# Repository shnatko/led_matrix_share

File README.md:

# led_matrix_share
Eagle files for LED matrix control board / analog mux array for IR sensing

Details on the build of the LED matrix ( in coffee table form ) can be found at http://shnatko.tumblr.com

The control_FET files contain the schematic and board files for a single 8x8 common anode 8x8 RGB LED array driving via SPI 
from a microcontroller ( Arduino Due in my case ).
Multiple boards can be chained together to form larger arrays ( matrix I built using them is 16x32 )

The sense_mux files are for a second PCB used to multiplex 64 analog input signals down to 4 outputs pins for input into
the microcontroller.  Again, additional details on how it is used at http://shnatko.tumblr.com

Also included in this package is the MBI.lbr Eagle library in which I created a few components which I needed for the board layout.

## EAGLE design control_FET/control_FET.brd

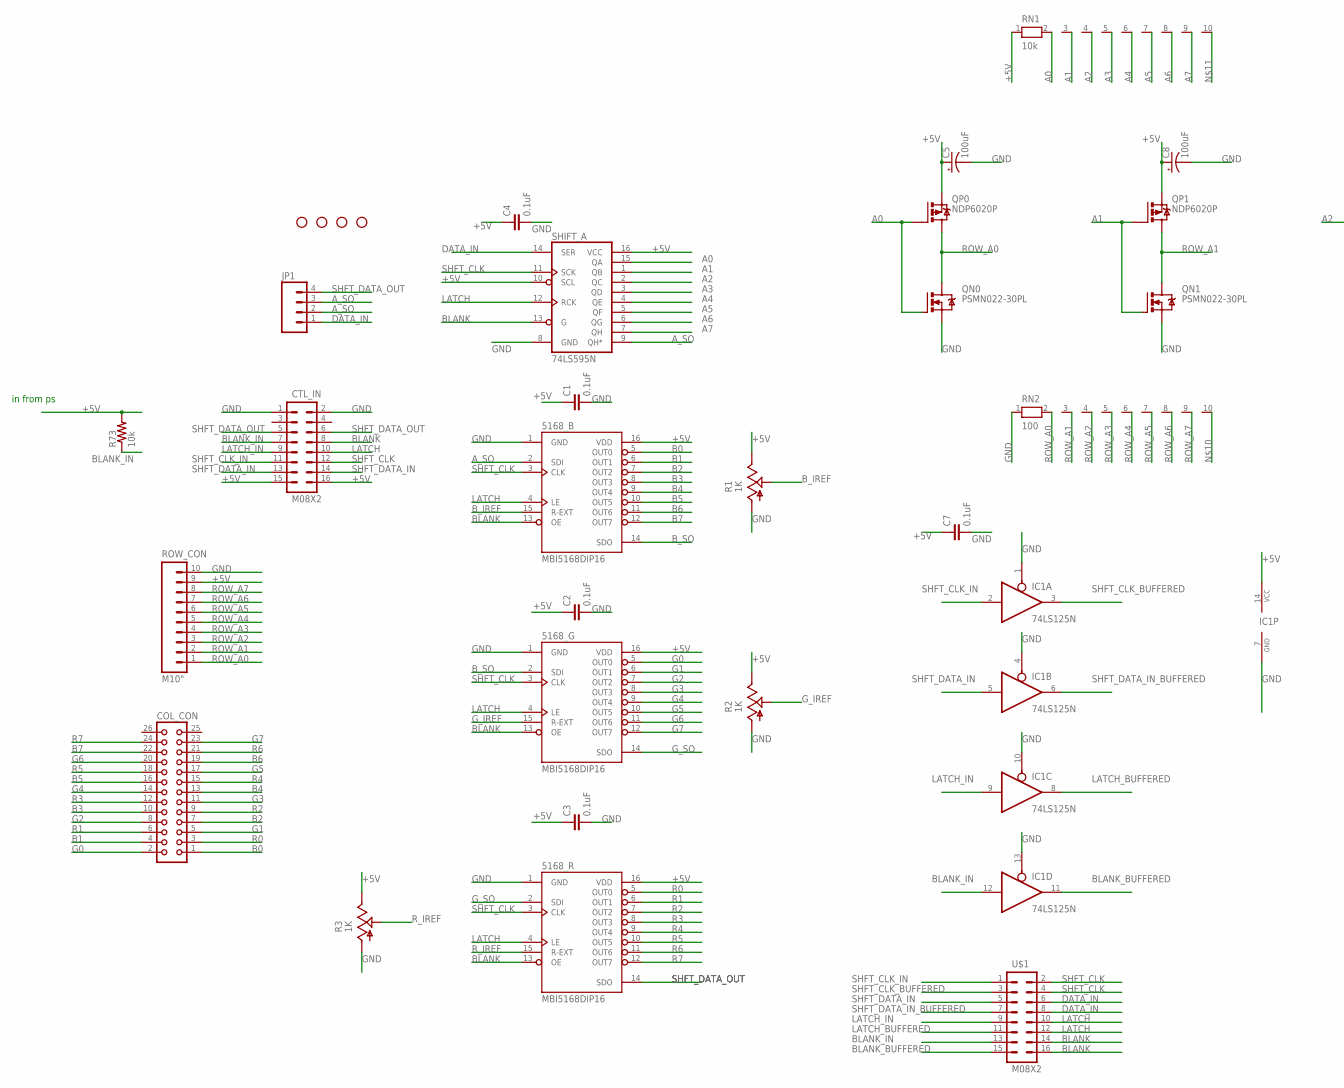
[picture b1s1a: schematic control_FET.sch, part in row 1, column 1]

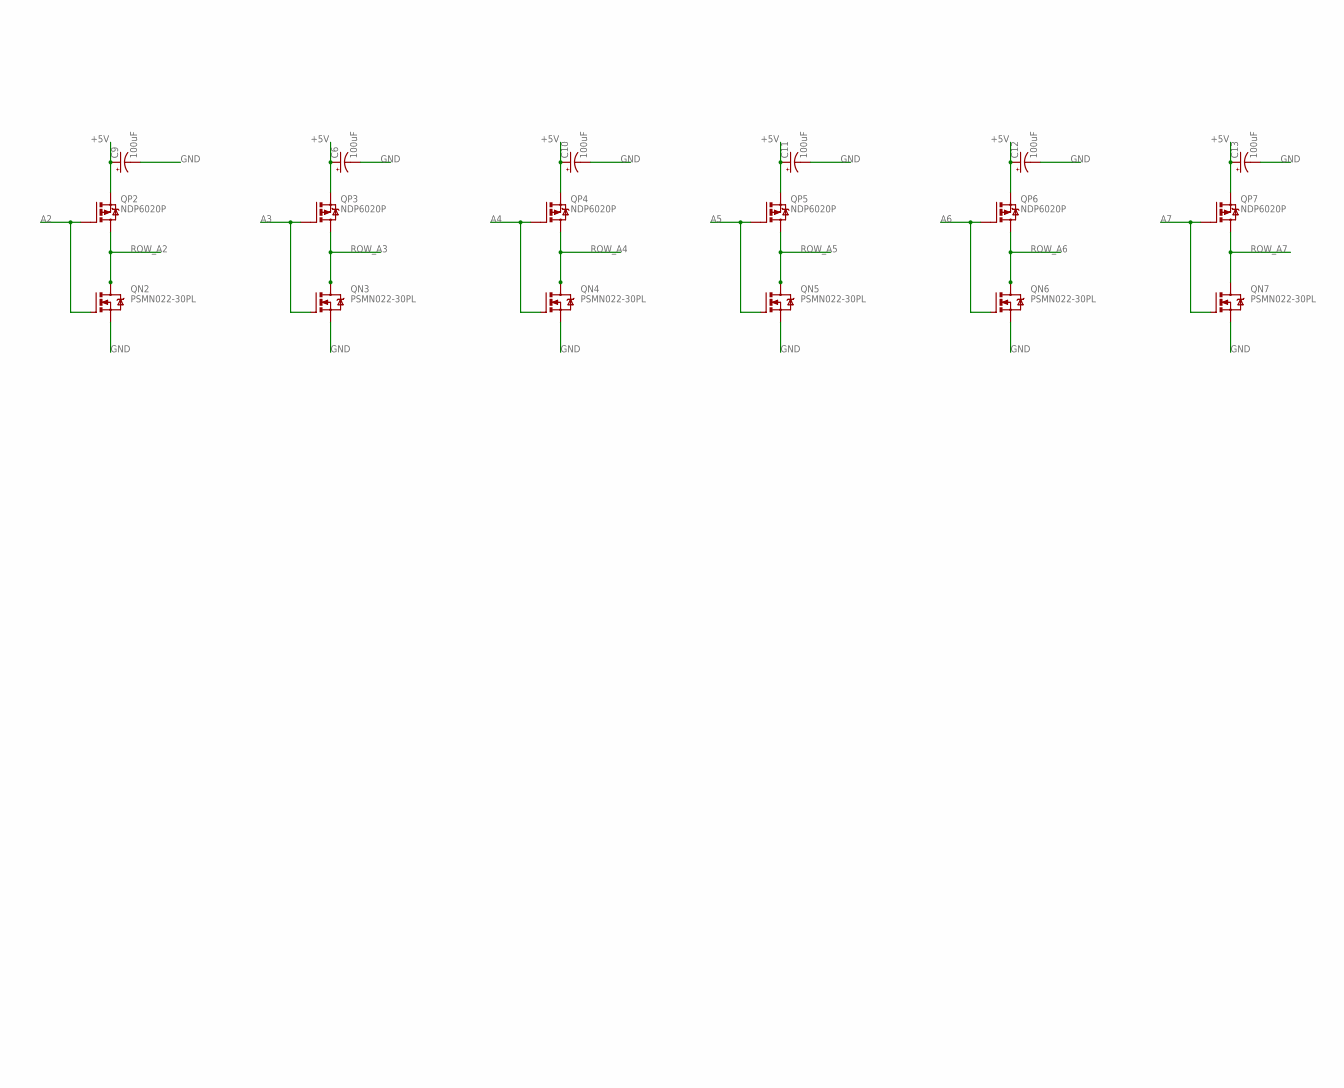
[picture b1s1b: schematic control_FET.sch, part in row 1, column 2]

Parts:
5168_B, 5168_G, 5168_R: MBI5168DIP16; DIL16
C1, C2, C3, C4, C7: 0.1uF; C2.5-3
C5, C6, C8, C9, C10, C11, C12, C13: 100uF; CPOL-RADIAL-100UF-25V
COL_CON: CON26
CTL_IN: M08X2; 2X8
IC1: 74LS125N; DIL14
JP1: M04PTH; 1X04
QN0, QN1, QN2, QN3, QN4, QN5, QN6, QN7: PSMN022-30PL; TO220BV
QP0, QP1, QP2, QP3, QP4, QP5, QP6, QP7: NDP6020P; TO220BV
R1, R2, R3: 1K; CA6V
R73: 10k; 0207/10
RN1: 10k; RN-10
RN2: 100; RN-10
ROW_CON: M10"; 1X10
SHIFT_A: 74LS595N; DIL16
STANDOFF1, STANDOFF2, STANDOFF3, STANDOFF4: STAND-OFF
U$1: M08X2; 2X8

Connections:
+5V: 5168_B.16 (VDD), 5168_G.16 (VDD), 5168_R.16 (VDD), C1.1, C2.1, C3.1, C4.1, C5.1 (+), C6.1 (+), C7.1, C8.1 (+), C9.1 (+), C10.1 (+), C11.1 (+), C12.1 (+), C13.1 (+), CTL_IN.15, CTL_IN.16, IC1.14 (VCC), QP0.S, QP1.S, QP2.S, QP3.S, QP4.S, QP5.S, QP6.S, QP7.S, R1.E, R2.E, R3.E, R73.2, RN1.1, ROW_CON.9, SHIFT_A.10 (SCL), SHIFT_A.16 (VCC)
A0: QN0.G, QP0.G, RN1.2, SHIFT_A.15 (QA)
A1: QN1.G, QP1.G, RN1.3, SHIFT_A.1 (QB)
A2: QN2.G, QP2.G, RN1.4, SHIFT_A.2 (QC)
A3: QN3.G, QP3.G, RN1.5, SHIFT_A.3 (QD)
A4: QN4.G, QP4.G, RN1.6, SHIFT_A.4 (QE)
A5: QN5.G, QP5.G, RN1.7, SHIFT_A.5 (QF)
A6: QN6.G, QP6.G, RN1.8, SHIFT_A.6 (QG)
A7: QN7.G, QP7.G, RN1.9, SHIFT_A.7 (QH)
A_SO: 5168_B.2 (SDI), JP1.2, JP1.3, SHIFT_A.9 (QH*)
B0: 5168_B.5 (OUT0), COL_CON.1
B1: 5168_B.6 (OUT1), COL_CON.4
B2: 5168_B.7 (OUT2), COL_CON.7
B3: 5168_B.8 (OUT3), COL_CON.10
B4: 5168_B.9 (OUT4), COL_CON.13
B5: 5168_B.10 (OUT5), COL_CON.16
B6: 5168_B.11 (OUT6), COL_CON.19
B7: 5168_B.12 (OUT7), COL_CON.22
BLANK: 5168_B.13 (OE), 5168_G.13 (OE), 5168_R.13 (OE), CTL_IN.8, SHIFT_A.13 (G), U$1.14, U$1.16
BLANK_BUFFERED: IC1.11 (O), U$1.15
BLANK_IN: CTL_IN.7, IC1.12 (I), R73.1, U$1.13
B_IREF: 5168_B.15 (R-EXT), R1.S
B_SO: 5168_B.14 (SDO), 5168_G.2 (SDI)
DATA_IN: JP1.1, SHIFT_A.14 (SER), U$1.6, U$1.8
G0: 5168_G.5 (OUT0), COL_CON.2
G1: 5168_G.6 (OUT1), COL_CON.5
G2: 5168_G.7 (OUT2), COL_CON.8
G3: 5168_G.8 (OUT3), COL_CON.11
G4: 5168_G.9 (OUT4), COL_CON.14
G5: 5168_G.10 (OUT5), COL_CON.17
G6: 5168_G.11 (OUT6), COL_CON.20
G7: 5168_G.12 (OUT7), COL_CON.23
GND: 5168_B.1 (GND), 5168_G.1 (GND), 5168_R.1 (GND), C1.2, C2.2, C3.2, C4.2, C5.2 (-), C6.2 (-), C7.2, C8.2 (-), C9.2 (-), C10.2 (-), C11.2 (-), C12.2 (-), C13.2 (-), CTL_IN.1, CTL_IN.2, IC1.1 (OE), IC1.4 (OE), IC1.7 (GND), IC1.10 (OE), IC1.13 (OE), QN0.S, QN1.S, QN2.S, QN3.S, QN4.S, QN5.S, QN6.S, QN7.S, R1.A, R2.A, R3.A, RN2.1, ROW_CON.10, SHIFT_A.8 (GND)
G_IREF: 5168_G.15 (R-EXT), R2.S
G_SO: 5168_G.14 (SDO), 5168_R.2 (SDI)
LATCH: 5168_B.4 (LE), 5168_G.4 (LE), 5168_R.4 (LE), CTL_IN.10, SHIFT_A.12 (RCK), U$1.10, U$1.12
LATCH_BUFFERED: IC1.8 (O), U$1.11
LATCH_IN: CTL_IN.9, IC1.9 (I), U$1.9
R0: 5168_R.5 (OUT0), COL_CON.3
R1: 5168_R.6 (OUT1), COL_CON.6
R2: 5168_R.7 (OUT2), COL_CON.9
R3: 5168_R.8 (OUT3), COL_CON.12
R4: 5168_R.9 (OUT4), COL_CON.15
R5: 5168_R.10 (OUT5), COL_CON.18
R6: 5168_R.11 (OUT6), COL_CON.21
R7: 5168_R.12 (OUT7), COL_CON.24
ROW_A0: QN0.D, QP0.D, RN2.2, ROW_CON.1
ROW_A1: QN1.D, QP1.D, RN2.3, ROW_CON.2
ROW_A2: QN2.D, QP2.D, RN2.4, ROW_CON.3
ROW_A3: QN3.D, QP3.D, RN2.5, ROW_CON.4
ROW_A4: QN4.D, QP4.D, RN2.6, ROW_CON.5
ROW_A5: QN5.D, QP5.D, RN2.7, ROW_CON.6
ROW_A6: QN6.D, QP6.D, RN2.8, ROW_CON.7
ROW_A7: QN7.D, QP7.D, RN2.9, ROW_CON.8
R_IREF: 5168_R.15 (R-EXT), R3.S
SHFT_CLK: 5168_B.3 (CLK), 5168_G.3 (CLK), 5168_R.3 (CLK), CTL_IN.12, SHIFT_A.11 (SCK), U$1.2, U$1.4
SHFT_CLK_BUFFERED: IC1.3 (O), U$1.3
SHFT_CLK_IN: CTL_IN.11, IC1.2 (I), U$1.1
SHFT_DATA_IN: CTL_IN.13, CTL_IN.14, IC1.5 (I), U$1.5
SHFT_DATA_IN_BUFFERED: IC1.6 (O), U$1.7
SHFT_DATA_OUT: 5168_R.14 (SDO), CTL_IN.5, CTL_IN.6, JP1.4

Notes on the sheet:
in from ps

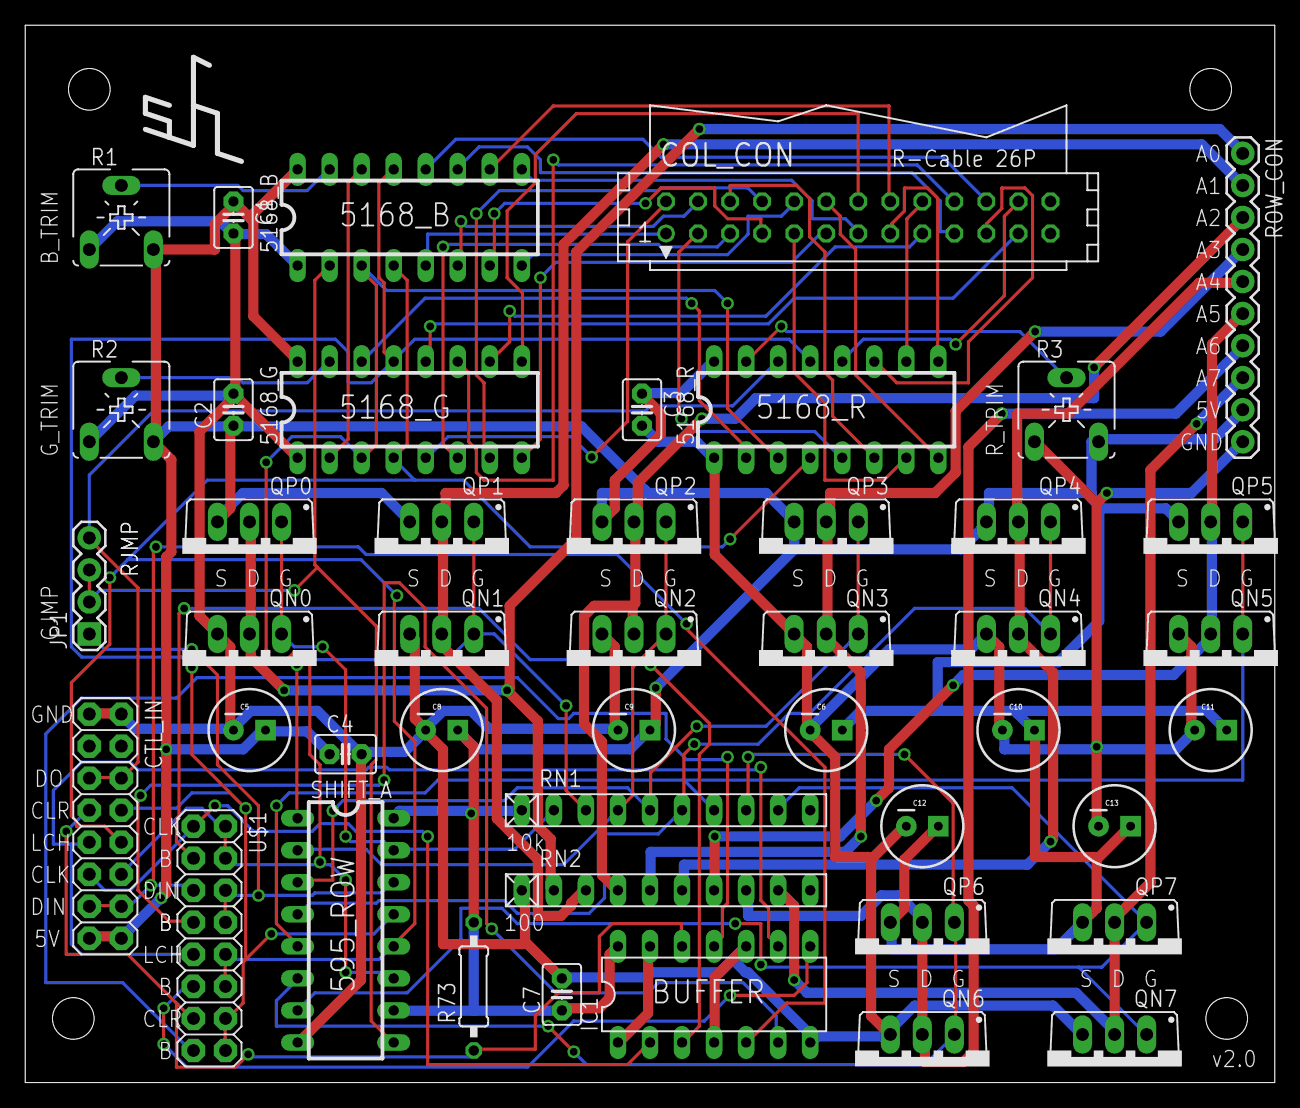
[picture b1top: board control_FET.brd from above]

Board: 2 copper layers, 99.1 x 83.8 mm, 49 parts (0 on the bottom side), 61 nets.

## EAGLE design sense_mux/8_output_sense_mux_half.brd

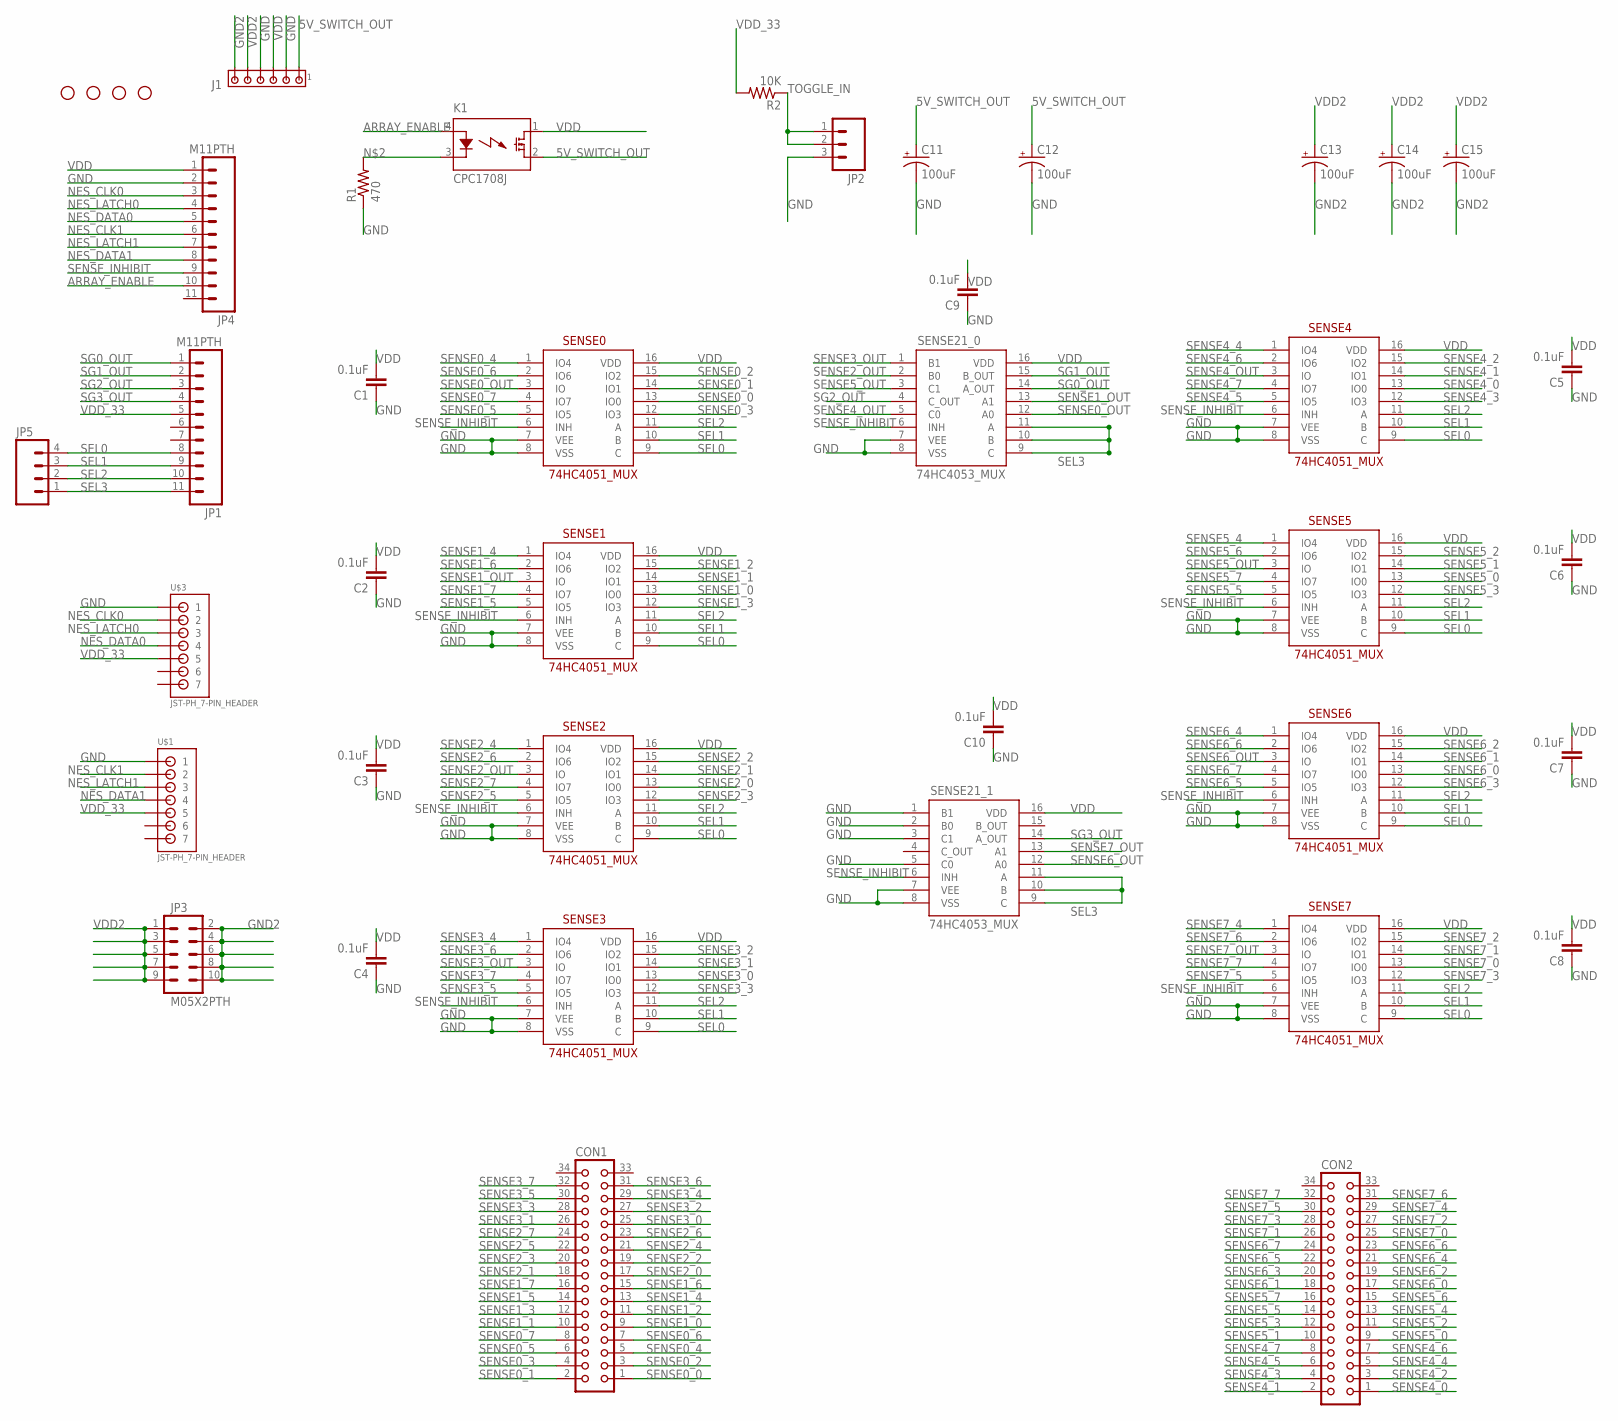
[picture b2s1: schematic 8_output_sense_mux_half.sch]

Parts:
C1, C2, C3, C4, C5, C6, C7, C8, C9, C10: 0.1uF; C2.5-3
C11, C12, C13, C14, C15: 100uF; CPOL-RADIAL-100UF-25V
CON1, CON2: CON34
J1: MTA06-156; 1X6MTA
JP1, JP4: M11PTH; 1X11
JP2: M03PTH; 1X03
JP3: M05X2PTH; AVR_ICSP
JP5: M04PTH; 1X04
K1: CPC1708J; I4-PAC
R1: 470; AXIAL-0.3-KIT
R2: 10K; AXIAL-0.3-KIT
SENSE0, SENSE1, SENSE2, SENSE3, SENSE4, SENSE5, SENSE6, SENSE7: 74HC4051_MUX; DIL16
SENSE21_0, SENSE21_1: 74HC4053_MUX; DIL16
STANDOFF1, STANDOFF2, STANDOFF3, STANDOFF4: STAND-OFF
U$1, U$3: JST-PH_7-PIN_HEADER; JST_B7B-PH_HEADER

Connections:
5V_SWITCH_OUT: C11.1 (+), C12.1 (+), J1.1, K1.2 (DS2)
ARRAY_ENABLE: JP4.10, K1.4 (A)
GND: C1.1, C2.1, C3.1, C4.1, C5.1, C6.1, C7.1, C8.1, C9.1, C10.1, C11.2 (-), C12.2 (-), J1.2, J1.4, JP2.3, JP4.2, R1.P$1 (1), SENSE0.7 (VEE), SENSE0.8 (VSS), SENSE1.7 (VEE), SENSE1.8 (VSS), SENSE2.7 (VEE), SENSE2.8 (VSS), SENSE3.7 (VEE), SENSE3.8 (VSS), SENSE4.7 (VEE), SENSE4.8 (VSS), SENSE5.7 (VEE), SENSE5.8 (VSS), SENSE6.7 (VEE), SENSE6.8 (VSS), SENSE7.7 (VEE), SENSE7.8 (VSS), SENSE21_0.7 (VEE), SENSE21_0.8 (VSS), SENSE21_1.1 (B1), SENSE21_1.2 (B0), SENSE21_1.3 (C1), SENSE21_1.5 (C0), SENSE21_1.7 (VEE), SENSE21_1.8 (VSS), U$1.P1 (1), U$3.P1 (1)
GND2: C13.2 (-), C14.2 (-), C15.2 (-), J1.6, JP3.2, JP3.4, JP3.6, JP3.8, JP3.10
unnamed: K1.3 (K), R1.P$2 (2)
NES_CLK0: JP4.3, U$3.P2 (2)
NES_CLK1: JP4.6, U$1.P2 (2)
NES_DATA0: JP4.5, U$3.P4 (4)
NES_DATA1: JP4.8, U$1.P4 (4)
NES_LATCH0: JP4.4, U$3.P3 (3)
NES_LATCH1: JP4.7, U$1.P3 (3)
SEL0: JP1.8, JP5.4, SENSE0.9 (C), SENSE1.9 (C), SENSE2.9 (C), SENSE3.9 (C), SENSE4.9 (C), SENSE5.9 (C), SENSE6.9 (C), SENSE7.9 (C)
SEL1: JP1.9, JP5.3, SENSE0.10 (B), SENSE1.10 (B), SENSE2.10 (B), SENSE3.10 (B), SENSE4.10 (B), SENSE5.10 (B), SENSE6.10 (B), SENSE7.10 (B)
SEL2: JP1.10, JP5.2, SENSE0.11 (A), SENSE1.11 (A), SENSE2.11 (A), SENSE3.11 (A), SENSE4.11 (A), SENSE5.11 (A), SENSE6.11 (A), SENSE7.11 (A)
SEL3: JP1.11, JP5.1, SENSE21_0.9 (C), SENSE21_0.10 (B), SENSE21_0.11 (A), SENSE21_1.9 (C), SENSE21_1.10 (B), SENSE21_1.11 (A)
SENSE0_0: CON1.1, SENSE0.13 (IO0)
SENSE0_1: CON1.2, SENSE0.14 (IO1)
SENSE0_2: CON1.3, SENSE0.15 (IO2)
SENSE0_3: CON1.4, SENSE0.12 (IO3)
SENSE0_4: CON1.5, SENSE0.1 (IO4)
SENSE0_5: CON1.6, SENSE0.5 (IO5)
SENSE0_6: CON1.7, SENSE0.2 (IO6)
SENSE0_7: CON1.8, SENSE0.4 (IO7)
SENSE0_OUT: SENSE0.3 (IO), SENSE21_0.12 (A0)
SENSE1_0: CON1.9, SENSE1.13 (IO0)
SENSE1_1: CON1.10, SENSE1.14 (IO1)
SENSE1_2: CON1.11, SENSE1.15 (IO2)
SENSE1_3: CON1.12, SENSE1.12 (IO3)
SENSE1_4: CON1.13, SENSE1.1 (IO4)
SENSE1_5: CON1.14, SENSE1.5 (IO5)
SENSE1_6: CON1.15, SENSE1.2 (IO6)
SENSE1_7: CON1.16, SENSE1.4 (IO7)
SENSE1_OUT: SENSE1.3 (IO), SENSE21_0.13 (A1)
SENSE2_0: CON1.17, SENSE2.13 (IO0)
SENSE2_1: CON1.18, SENSE2.14 (IO1)
SENSE2_2: CON1.19, SENSE2.15 (IO2)
SENSE2_3: CON1.20, SENSE2.12 (IO3)
SENSE2_4: CON1.21, SENSE2.1 (IO4)
SENSE2_5: CON1.22, SENSE2.5 (IO5)
SENSE2_6: CON1.23, SENSE2.2 (IO6)
SENSE2_7: CON1.24, SENSE2.4 (IO7)
SENSE2_OUT: SENSE2.3 (IO), SENSE21_0.2 (B0)
SENSE3_0: CON1.25, SENSE3.13 (IO0)
SENSE3_1: CON1.26, SENSE3.14 (IO1)
SENSE3_2: CON1.27, SENSE3.15 (IO2)
SENSE3_3: CON1.28, SENSE3.12 (IO3)
SENSE3_4: CON1.29, SENSE3.1 (IO4)
SENSE3_5: CON1.30, SENSE3.5 (IO5)
SENSE3_6: CON1.31, SENSE3.2 (IO6)
SENSE3_7: CON1.32, SENSE3.4 (IO7)
SENSE3_OUT: SENSE3.3 (IO), SENSE21_0.1 (B1)
SENSE4_0: CON2.1, SENSE4.13 (IO0)
SENSE4_1: CON2.2, SENSE4.14 (IO1)
SENSE4_2: CON2.3, SENSE4.15 (IO2)
SENSE4_3: CON2.4, SENSE4.12 (IO3)
SENSE4_4: CON2.5, SENSE4.1 (IO4)
SENSE4_5: CON2.6, SENSE4.5 (IO5)
SENSE4_6: CON2.7, SENSE4.2 (IO6)
SENSE4_7: CON2.8, SENSE4.4 (IO7)
SENSE4_OUT: SENSE4.3 (IO), SENSE21_0.5 (C0)
SENSE5_0: CON2.9, SENSE5.13 (IO0)
SENSE5_1: CON2.10, SENSE5.14 (IO1)
SENSE5_2: CON2.11, SENSE5.15 (IO2)
SENSE5_3: CON2.12, SENSE5.12 (IO3)
SENSE5_4: CON2.13, SENSE5.1 (IO4)
SENSE5_5: CON2.14, SENSE5.5 (IO5)
SENSE5_6: CON2.15, SENSE5.2 (IO6)
SENSE5_7: CON2.16, SENSE5.4 (IO7)
SENSE5_OUT: SENSE5.3 (IO), SENSE21_0.3 (C1)
SENSE6_0: CON2.17, SENSE6.13 (IO0)
SENSE6_1: CON2.18, SENSE6.14 (IO1)
SENSE6_2: CON2.19, SENSE6.15 (IO2)
SENSE6_3: CON2.20, SENSE6.12 (IO3)
SENSE6_4: CON2.21, SENSE6.1 (IO4)
SENSE6_5: CON2.22, SENSE6.5 (IO5)
SENSE6_6: CON2.23, SENSE6.2 (IO6)
SENSE6_7: CON2.24, SENSE6.4 (IO7)
SENSE6_OUT: SENSE6.3 (IO), SENSE21_1.12 (A0)
SENSE7_0: CON2.25, SENSE7.13 (IO0)
SENSE7_1: CON2.26, SENSE7.14 (IO1)
SENSE7_2: CON2.27, SENSE7.15 (IO2)
SENSE7_3: CON2.28, SENSE7.12 (IO3)
SENSE7_4: CON2.29, SENSE7.1 (IO4)
SENSE7_5: CON2.30, SENSE7.5 (IO5)
SENSE7_6: CON2.31, SENSE7.2 (IO6)
SENSE7_7: CON2.32, SENSE7.4 (IO7)
SENSE7_OUT: SENSE7.3 (IO), SENSE21_1.13 (A1)
SENSE_INHIBIT: JP4.9, SENSE0.6 (INH), SENSE1.6 (INH), SENSE2.6 (INH), SENSE3.6 (INH), SENSE4.6 (INH), SENSE5.6 (INH), SENSE6.6 (INH), SENSE7.6 (INH), SENSE21_0.6 (INH), SENSE21_1.6 (INH)
SG0_OUT: JP1.1, SENSE21_0.14 (A_OUT)
SG1_OUT: JP1.2, SENSE21_0.15 (B_OUT)
SG2_OUT: JP1.3, SENSE21_0.4 (C_OUT)
SG3_OUT: JP1.4, SENSE21_1.14 (A_OUT)
TOGGLE_IN: JP2.1, JP2.2, R2.P$1 (1)
VDD: C1.2, C2.2, C3.2, C4.2, C5.2, C6.2, C7.2, C8.2, C9.2, C10.2, J1.3, JP4.1, K1.1 (DS1), SENSE0.16 (VDD), SENSE1.16 (VDD), SENSE2.16 (VDD), SENSE3.16 (VDD), SENSE4.16 (VDD), SENSE5.16 (VDD), SENSE6.16 (VDD), SENSE7.16 (VDD), SENSE21_0.16 (VDD), SENSE21_1.16 (VDD)
VDD2: C13.1 (+), C14.1 (+), C15.1 (+), J1.5, JP3.1, JP3.3, JP3.5, JP3.7, JP3.9
VDD_33: JP1.5, R2.P$2 (2), U$1.P5 (5), U$3.P5 (5)

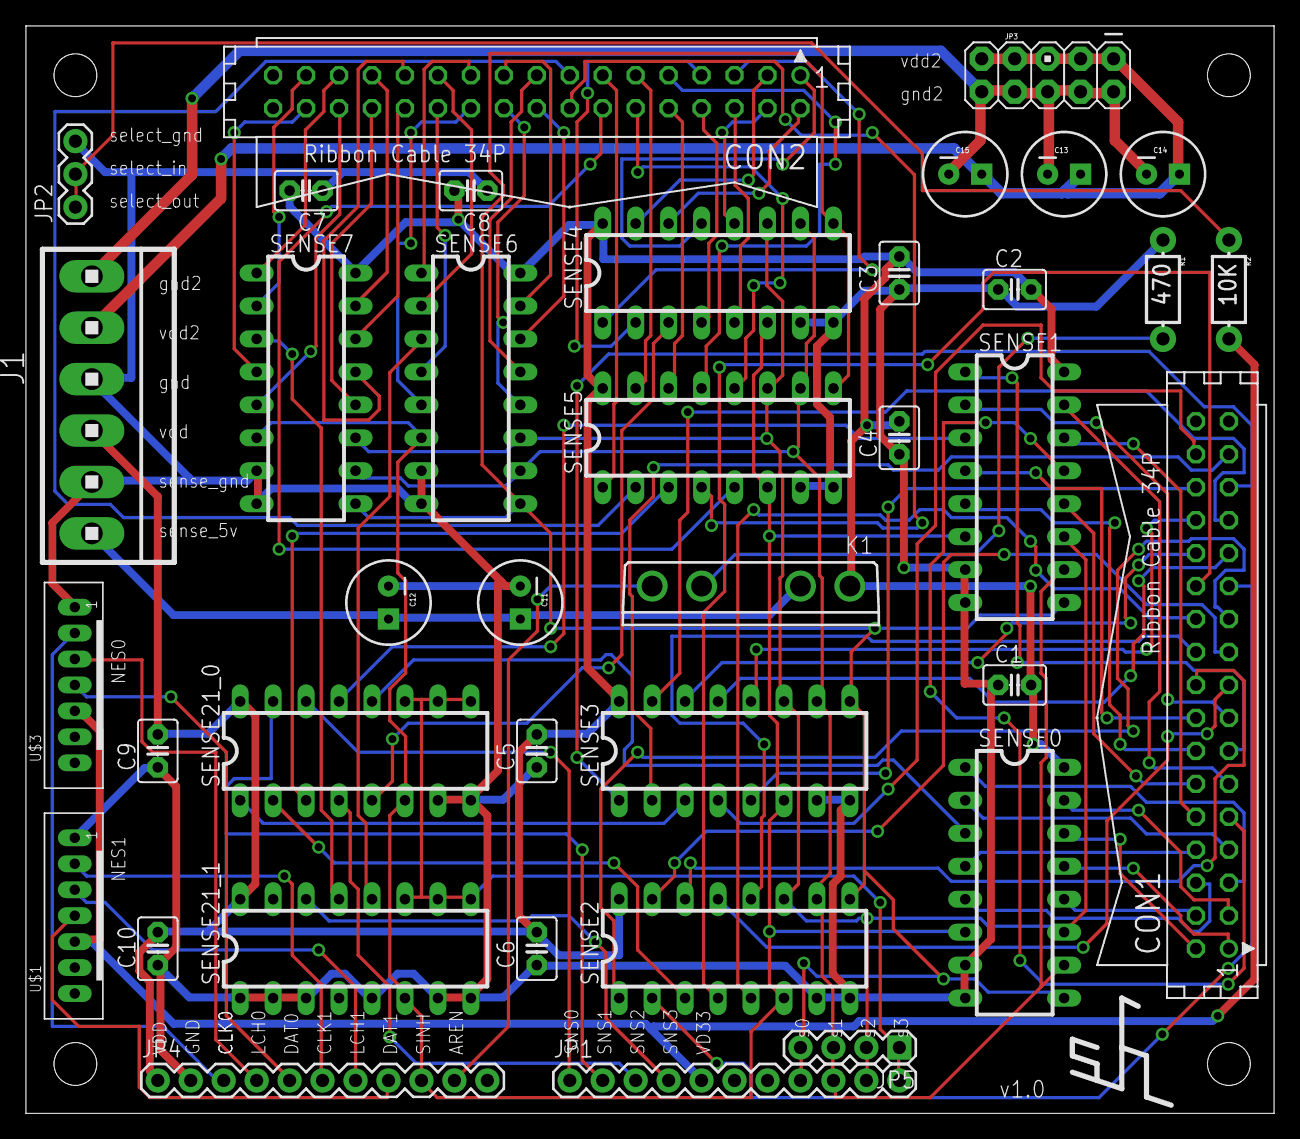
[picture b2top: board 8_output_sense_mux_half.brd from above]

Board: 2 copper layers, 96.2 x 83.8 mm, 43 parts (0 on the bottom side), 96 nets.

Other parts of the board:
U$2: SH

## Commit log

2015-06-18 :circus_tent: Added .gitattributes & .gitignore files
2015-06-18 Eagle files for LED array control boards and IR sense mux arrays
    Eagle files for FET control board which drives LED array and second PCB
    for the IR matrix analog muxes / misc controls

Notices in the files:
parts and their libraries:
SparkFun-DigitalIC: Licensing: CC v3.0 Share-Alike You are welcome to use this library for commercial purposes.
